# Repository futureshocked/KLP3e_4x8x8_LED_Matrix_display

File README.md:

# KLP3e 4x8x8 LED Matrix, a Kicad project

This is the repository for the "4x8x8 LED Matrix display" project.

This is one of the projects from the course [KiCad Like a Pro, 3rd edition](https://techexplorations.com/so/kicad-like-a-pro-3rd-edition/).

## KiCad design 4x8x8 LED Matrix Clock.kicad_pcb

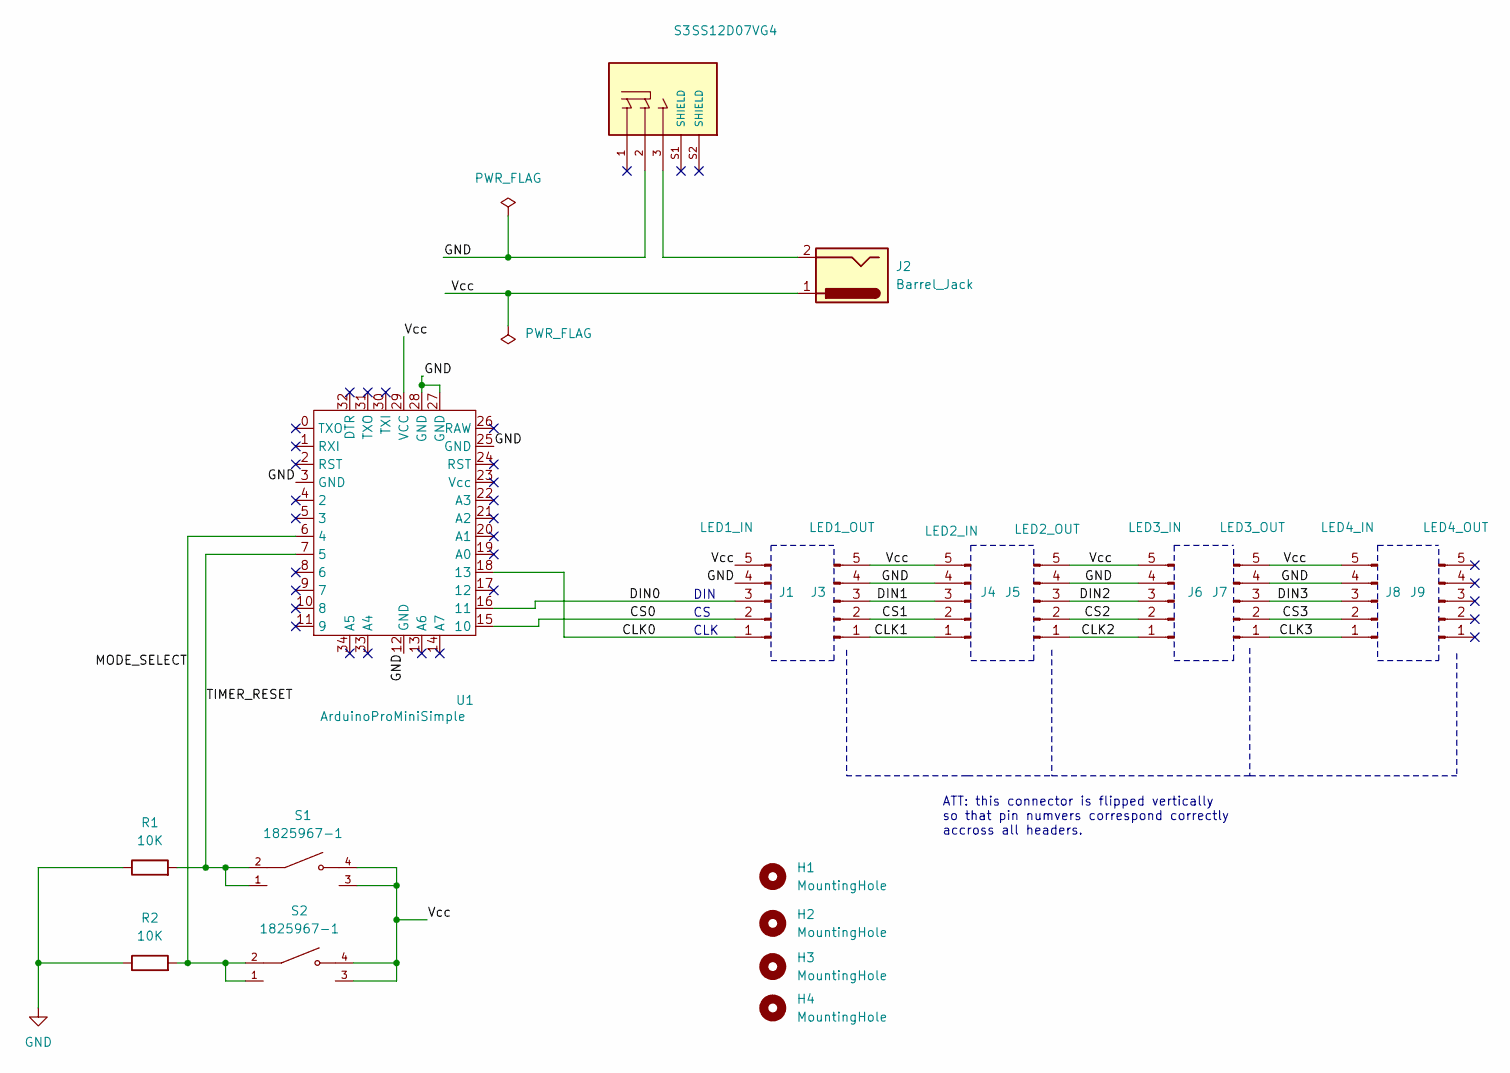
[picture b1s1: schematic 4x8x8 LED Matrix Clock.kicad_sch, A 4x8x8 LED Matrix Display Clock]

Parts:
H1, H2, H3, H4: MountingHole; MountingHole_2.5mm
J1: LED1_IN; PinHeader_1x05_P2.54mm_Vertical
J2: Barrel_Jack; BarrelJack_Horizontal
J3: LED1_OUT; PinSocket_1x05_P2.54mm_Vertical
J4: LED2_IN; PinSocket_1x05_P2.54mm_Vertical
J5: LED2_OUT; PinSocket_1x05_P2.54mm_Vertical
J6: LED3_IN; PinSocket_1x05_P2.54mm_Vertical
J7: LED3_OUT; PinSocket_1x05_P2.54mm_Vertical
J8: LED4_IN; PinSocket_1x05_P2.54mm_Vertical
J9: LED4_OUT; PinSocket_1x05_P2.54mm_Vertical
R1, R2: 10K; R_Axial_DIN0204_L3.6mm_D1.6mm_P7.62mm_Horizontal
S1, S2: 1825967-1; SW_1825967-1
S3: SS12D07VG4; SW_SS12D07VG4; PARTREV 1
U1: ArduinoProMiniSimple; ArduinoProMiniCustom

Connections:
/CLK0: J1.1, U1.18 (13)
/CLK1: J3.1, J4.1
/CLK2: J5.1, J6.1
/CLK3: J7.1, J8.1
/CS0: J1.2, U1.15 (10)
/CS1: J3.2, J4.2
/CS2: J5.2, J6.2
/CS3: J7.2, J8.2
/DIN0: J1.3, U1.16 (11)
/DIN1: J3.3, J4.3
/DIN2: J5.3, J6.3
/DIN3: J7.3, J8.3
/MODE_SELECT: R2.2, S2.1, S2.2, U1.6 (4)
/TIMER_RESET: R1.2, S1.1, S1.2, U1.7 (5)
/Vcc: J1.5, J2.1, J3.5, J4.5, J5.5, J6.5, J7.5, J8.5, S1.3, S1.4, S2.3, S2.4, U1.29 (VCC)
GND: J1.4, J3.4, J4.4, J5.4, J6.4, J7.4, J8.4, R1.1, R2.1, S3.2, U1.3 (GND), U1.12 (GND), U1.25 (GND), U1.27 (GND), U1.28 (GND)
unnamed: J2.2, S3.3

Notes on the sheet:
DIN
CLK
ATT: this connector is flipped vertically so that pin numvers correspond correctly accross all headers.

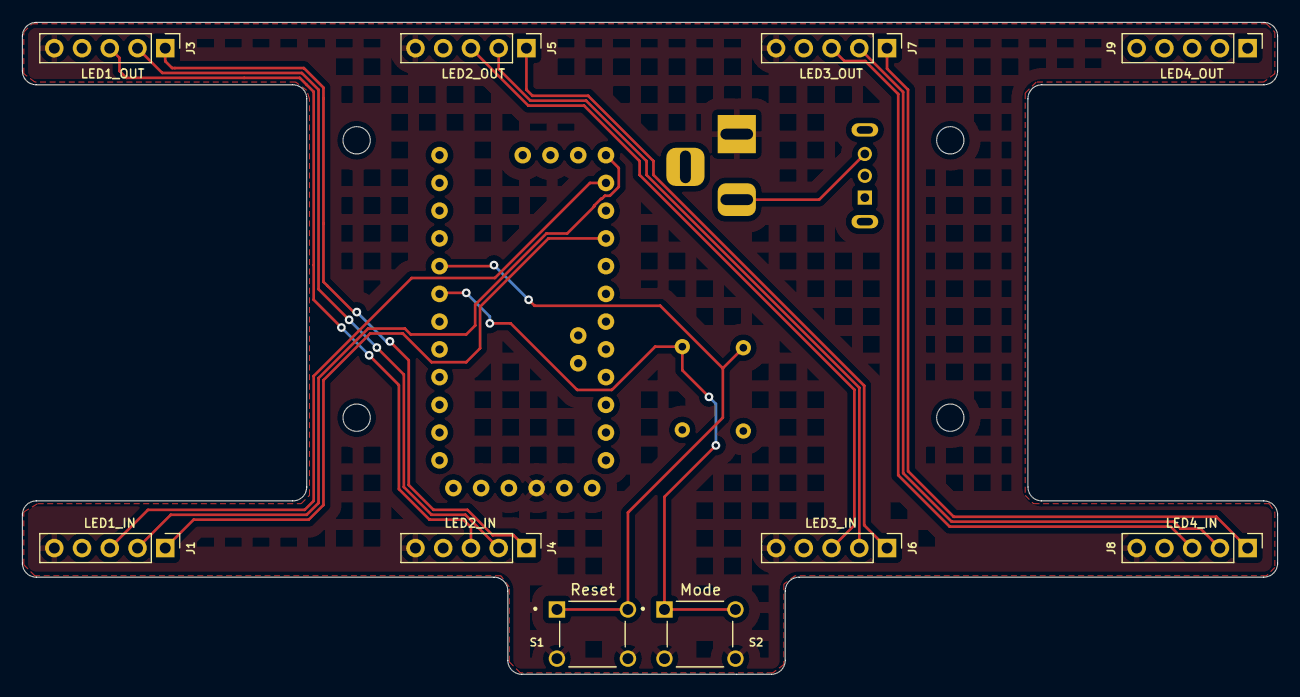
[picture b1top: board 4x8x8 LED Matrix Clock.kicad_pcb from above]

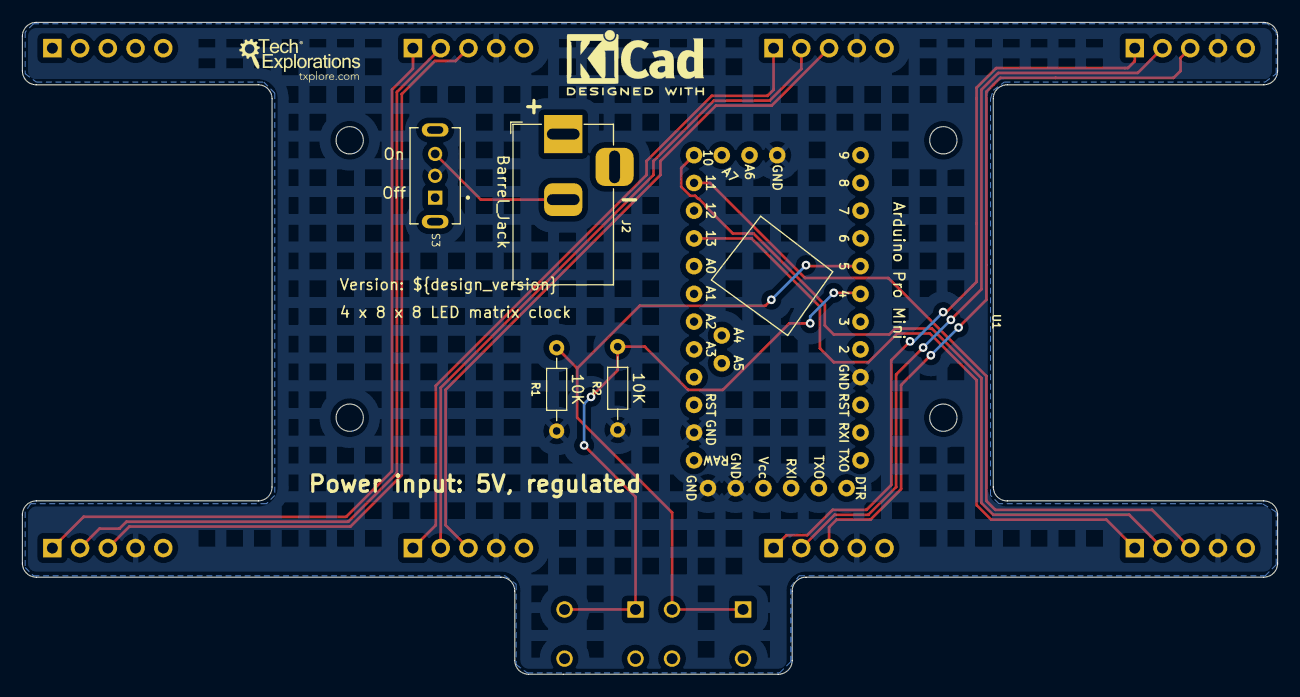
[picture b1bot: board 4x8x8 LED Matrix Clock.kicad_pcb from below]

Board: 2 copper layers, 114.9 x 59.7 mm, 19 parts (5 on the bottom side), 17 nets.
